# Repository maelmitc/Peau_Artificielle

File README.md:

# $${\color{black}Peau \space \color{black}artificielle\space \color{black}appliqué\space \color{black}à\space \color{black}un\space \color{black}robot\space \color{black}par\space \color{black}IA}$$

$${\color{black}Objectif\space\color{black}du\space\color{black}projet\color{black}}$$
Ce projet à pour but d'appliqué à un robot déjà conçu (**REACHY**) une interface tactile dans le but de lui permettre d'interragir socialement au contat physique.

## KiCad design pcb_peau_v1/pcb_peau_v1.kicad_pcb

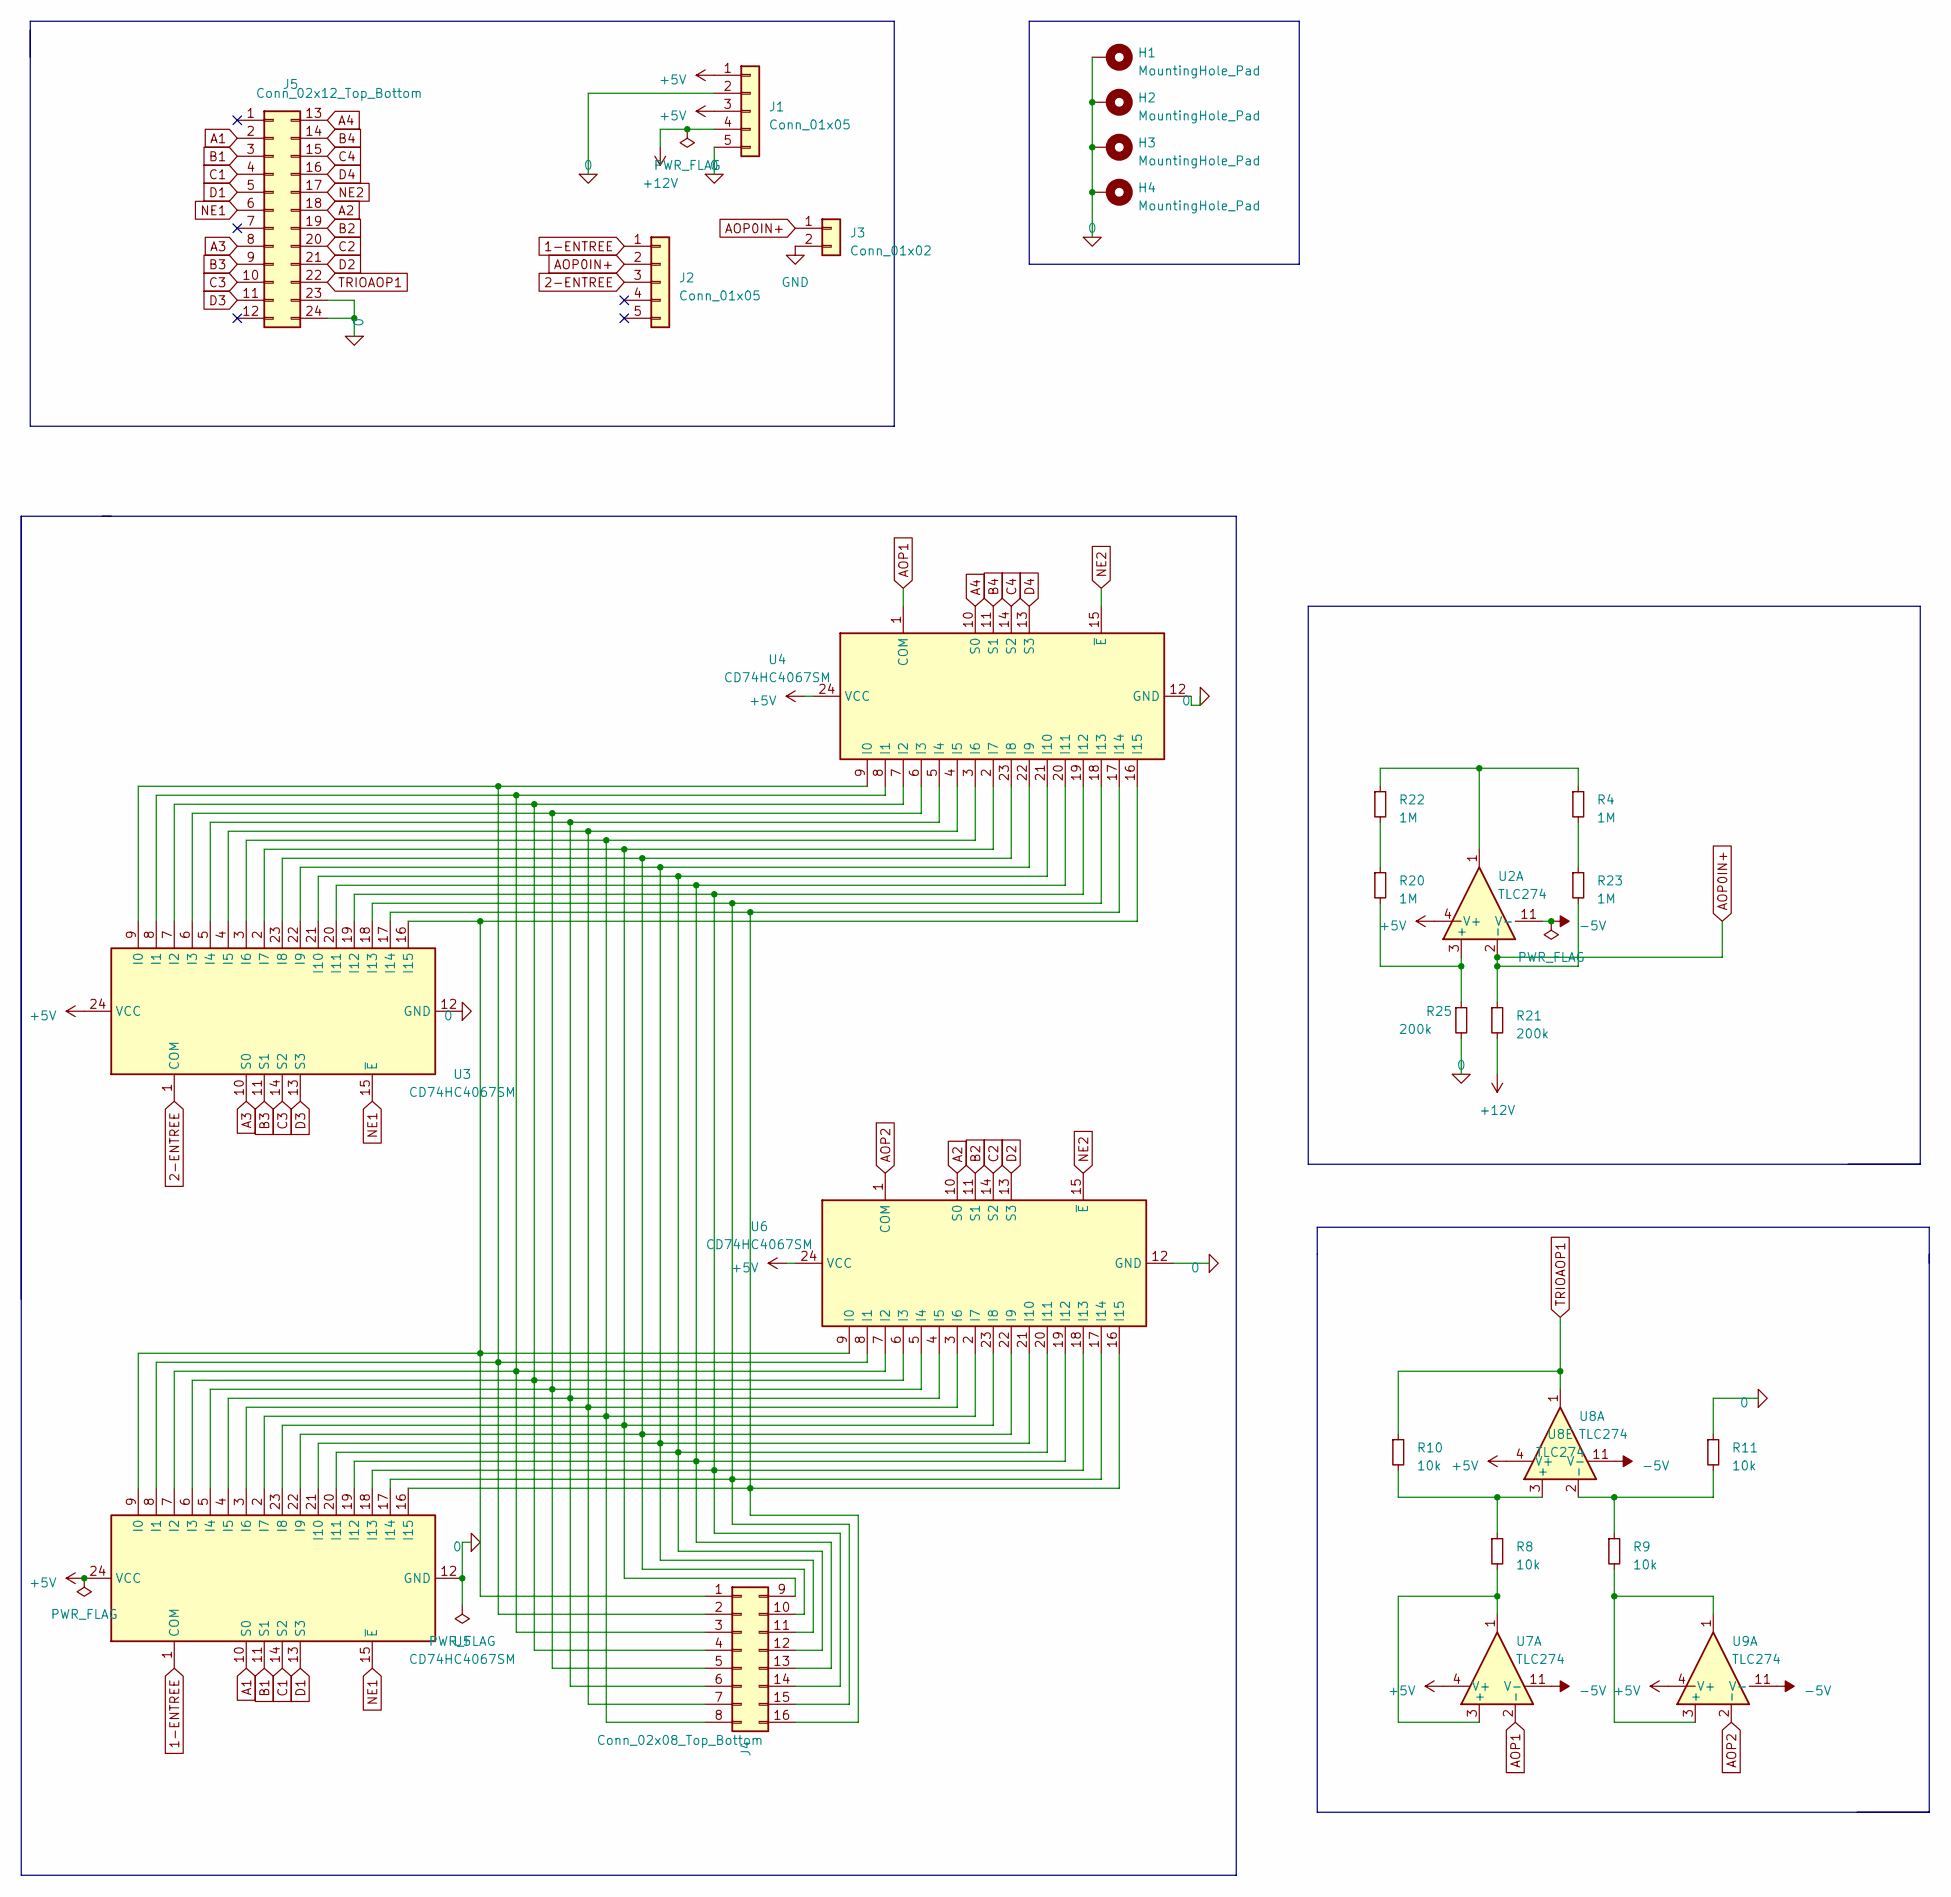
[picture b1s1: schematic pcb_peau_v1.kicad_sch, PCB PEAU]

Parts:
H1, H2, H3, H4: MountingHole_Pad; MountingHole_3.2mm_M3_DIN965_Pad
J1, J2: Conn_01x05; JST_EH_B5B-EH-A_1x05_P2.50mm_Vertical
J3: Conn_01x02; JST_EH_B2B-EH-A_1x02_P2.50mm_Vertical
J4: Conn_02x08_Top_Bottom; JST_PHD_B16B-PHDSS_2x08_P2.00mm_Vertical
J5: Conn_02x12_Top_Bottom; JST_PHD_B24B-PHDSS_2x12_P2.00mm_Vertical
R4, R20, R22, R23: 1M; R_0603_1608Metric_Pad0.98x0.95mm_HandSolder
R8, R9, R10, R11: 10k; R_0603_1608Metric_Pad0.98x0.95mm_HandSolder
R21, R25: 200k; R_0603_1608Metric_Pad0.98x0.95mm_HandSolder
U2, U7, U8, U9: TLC274; SO14
U3, U4, U5, U6: CD74HC4067SM; SSOP-24_5.3x8.2mm_P0.65mm

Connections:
0: H1.1, H2.1, H3.1, H4.1, J1.2, J1.5, J5.23, J5.24, R11.1, R25.2, U3.12 (GND), U4.12 (GND), U5.12 (GND), U6.12 (GND)
1-ENTREE: J2.1, U5.1 (COM)
2-ENTREE: J2.3, U3.1 (COM)
+5V: J1.1, J1.3, U2.4 (V+), U3.24 (VCC), U4.24 (VCC), U5.24 (VCC), U6.24 (VCC), U7.4 (V+), U8.4 (V+), U9.4 (V+)
+12V: J1.4, R21.2
-5V: U2.11 (V-), U7.11 (V-), U8.11 (V-), U9.11 (V-)
A1: J5.2, U5.10 (S0)
A2: J5.18, U6.10 (S0)
A3: J5.8, U3.10 (S0)
A4: J5.13, U4.10 (S0)
AOP0IN+: J2.2, J3.1, R21.1, R23.2, U2.2 (-)
AOP1: U4.1 (COM), U7.2 (-)
AOP2: U6.1 (COM), U9.2 (-)
B1: J5.3, U5.11 (S1)
B2: J5.19, U6.11 (S1)
B3: J5.9, U3.11 (S1)
B4: J5.14, U4.11 (S1)
C1: J5.4, U5.14 (S2)
C2: J5.20, U6.14 (S2)
C3: J5.10, U3.14 (S2)
C4: J5.15, U4.14 (S2)
D1: J5.5, U5.13 (S3)
D2: J5.21, U6.13 (S3)
D3: J5.11, U3.13 (S3)
D4: J5.16, U4.13 (S3)
GND: J3.2
NE1: J5.6, U3.15 (~E), U5.15 (~E)
NE2: J5.17, U4.15 (~E), U6.15 (~E)
unnamed: J4.1, U3.16 (I15), U4.16 (I15), U5.9 (I0), U6.9 (I0)
unnamed: J4.2, U3.9 (I0), U4.9 (I0), U5.8 (I1), U6.8 (I1)
unnamed: J4.3, U3.8 (I1), U4.8 (I1), U5.7 (I2), U6.7 (I2)
unnamed: J4.4, U3.7 (I2), U4.7 (I2), U5.6 (I3), U6.6 (I3)
unnamed: J4.5, U3.6 (I3), U4.6 (I3), U5.5 (I4), U6.5 (I4)
unnamed: J4.6, U3.5 (I4), U4.5 (I4), U5.4 (I5), U6.4 (I5)
unnamed: J4.7, U3.4 (I5), U4.4 (I5), U5.3 (I6), U6.3 (I6)
unnamed: J4.8, U3.3 (I6), U4.3 (I6), U5.2 (I7), U6.2 (I7)
unnamed: J4.9, U3.2 (I7), U4.2 (I7), U5.23 (I8), U6.23 (I8)
unnamed: J4.10, U3.23 (I8), U4.23 (I8), U5.22 (I9), U6.22 (I9)
unnamed: J4.11, U3.22 (I9), U4.22 (I9), U5.21 (I10), U6.21 (I10)
unnamed: J4.12, U3.21 (I10), U4.21 (I10), U5.20 (I11), U6.20 (I11)
unnamed: J4.13, U3.20 (I11), U4.20 (I11), U5.19 (I12), U6.19 (I12)
unnamed: J4.14, U3.19 (I12), U4.19 (I12), U5.18 (I13), U6.18 (I13)
unnamed: J4.15, U3.18 (I13), U4.18 (I13), U5.17 (I14), U6.17 (I14)
unnamed: J4.16, U3.17 (I14), U4.17 (I14), U5.16 (I15), U6.16 (I15)
unnamed: R20.1, R22.2
unnamed: R4.1, R22.1, U2.1
unnamed: R4.2, R23.1
unnamed: R20.2, R25.1, U2.3 (+)
unnamed: R8.2, U7.1, U7.3 (+)
unnamed: R8.1, R10.2, U8.3 (+)
unnamed: R9.1, R11.2, U8.2 (-)
unnamed: R9.2, U9.1, U9.3 (+)
TRIOAOP1: J5.22, R10.1, U8.1

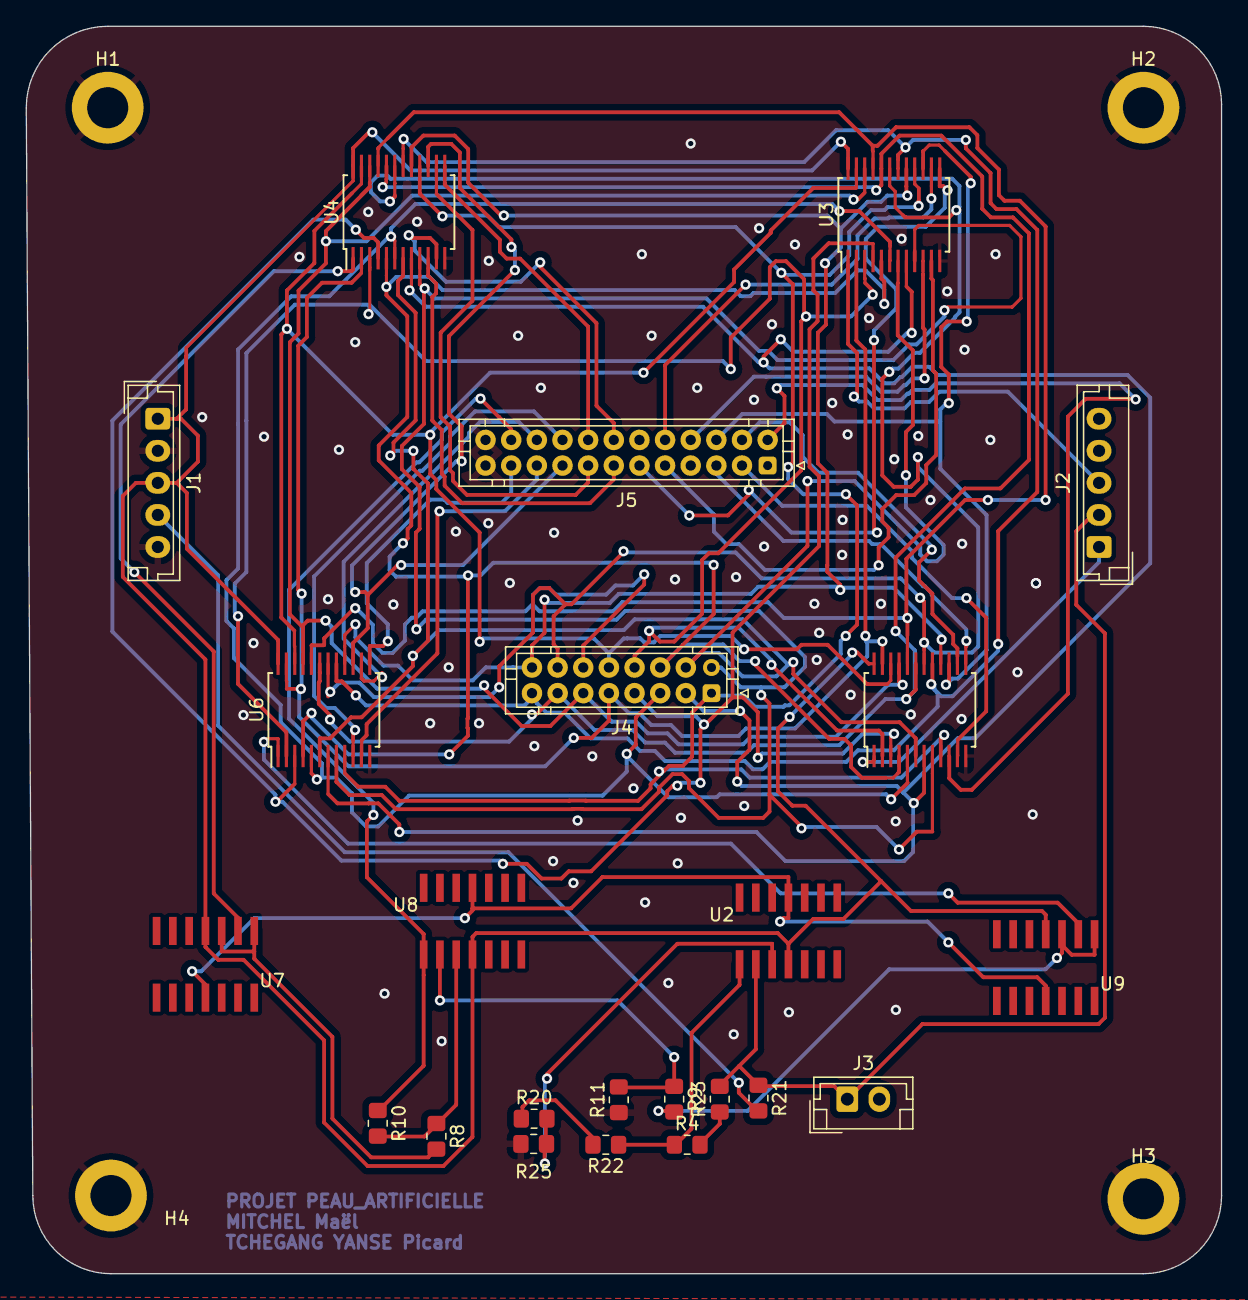
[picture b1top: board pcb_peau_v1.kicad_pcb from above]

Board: 2 copper layers, 93.2 x 97.3 mm, 27 parts (0 on the bottom side), 52 nets.

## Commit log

2023-11-14 Schématic Kicad
2023-11-14 Schématic maj
2023-11-21 Schématic
2023-12-05 Modification schematic
2023-12-05 PCB footprints en cours
2023-12-08 auto save
2023-12-09 Début du PCB
2023-12-12 Add files via upload
    Voici le GANTT
2023-12-12 PCB début
2023-12-19 PCB Mux/demux
2024-01-16 PCB avancé
2024-01-23 Kicad tout connecté
    Kicad tout connecté
2024-01-23 PCB FINI
2024-02-05 PCB corrigé
2024-02-27 Modif
2024-02-27 Mise a jour avec les bonnes dimensions
2024-02-29 Pcb Corrigé presque pret
2024-03-05 PCB au bonnes normes (on y croit)
2024-03-07 Optimisation du cuivre
2024-03-07 Génération des drills / gerbers
2024-03-09 fichier pour patricia
2024-03-19 pdb bulletproof
2024-04-02 ça marche pas
2024-04-02 Code de simulation de la peau + kohonen et dataset
2024-04-10 Rapport de projet
2024-04-10 Depot final de projet
2024-04-18 Demonstration video
